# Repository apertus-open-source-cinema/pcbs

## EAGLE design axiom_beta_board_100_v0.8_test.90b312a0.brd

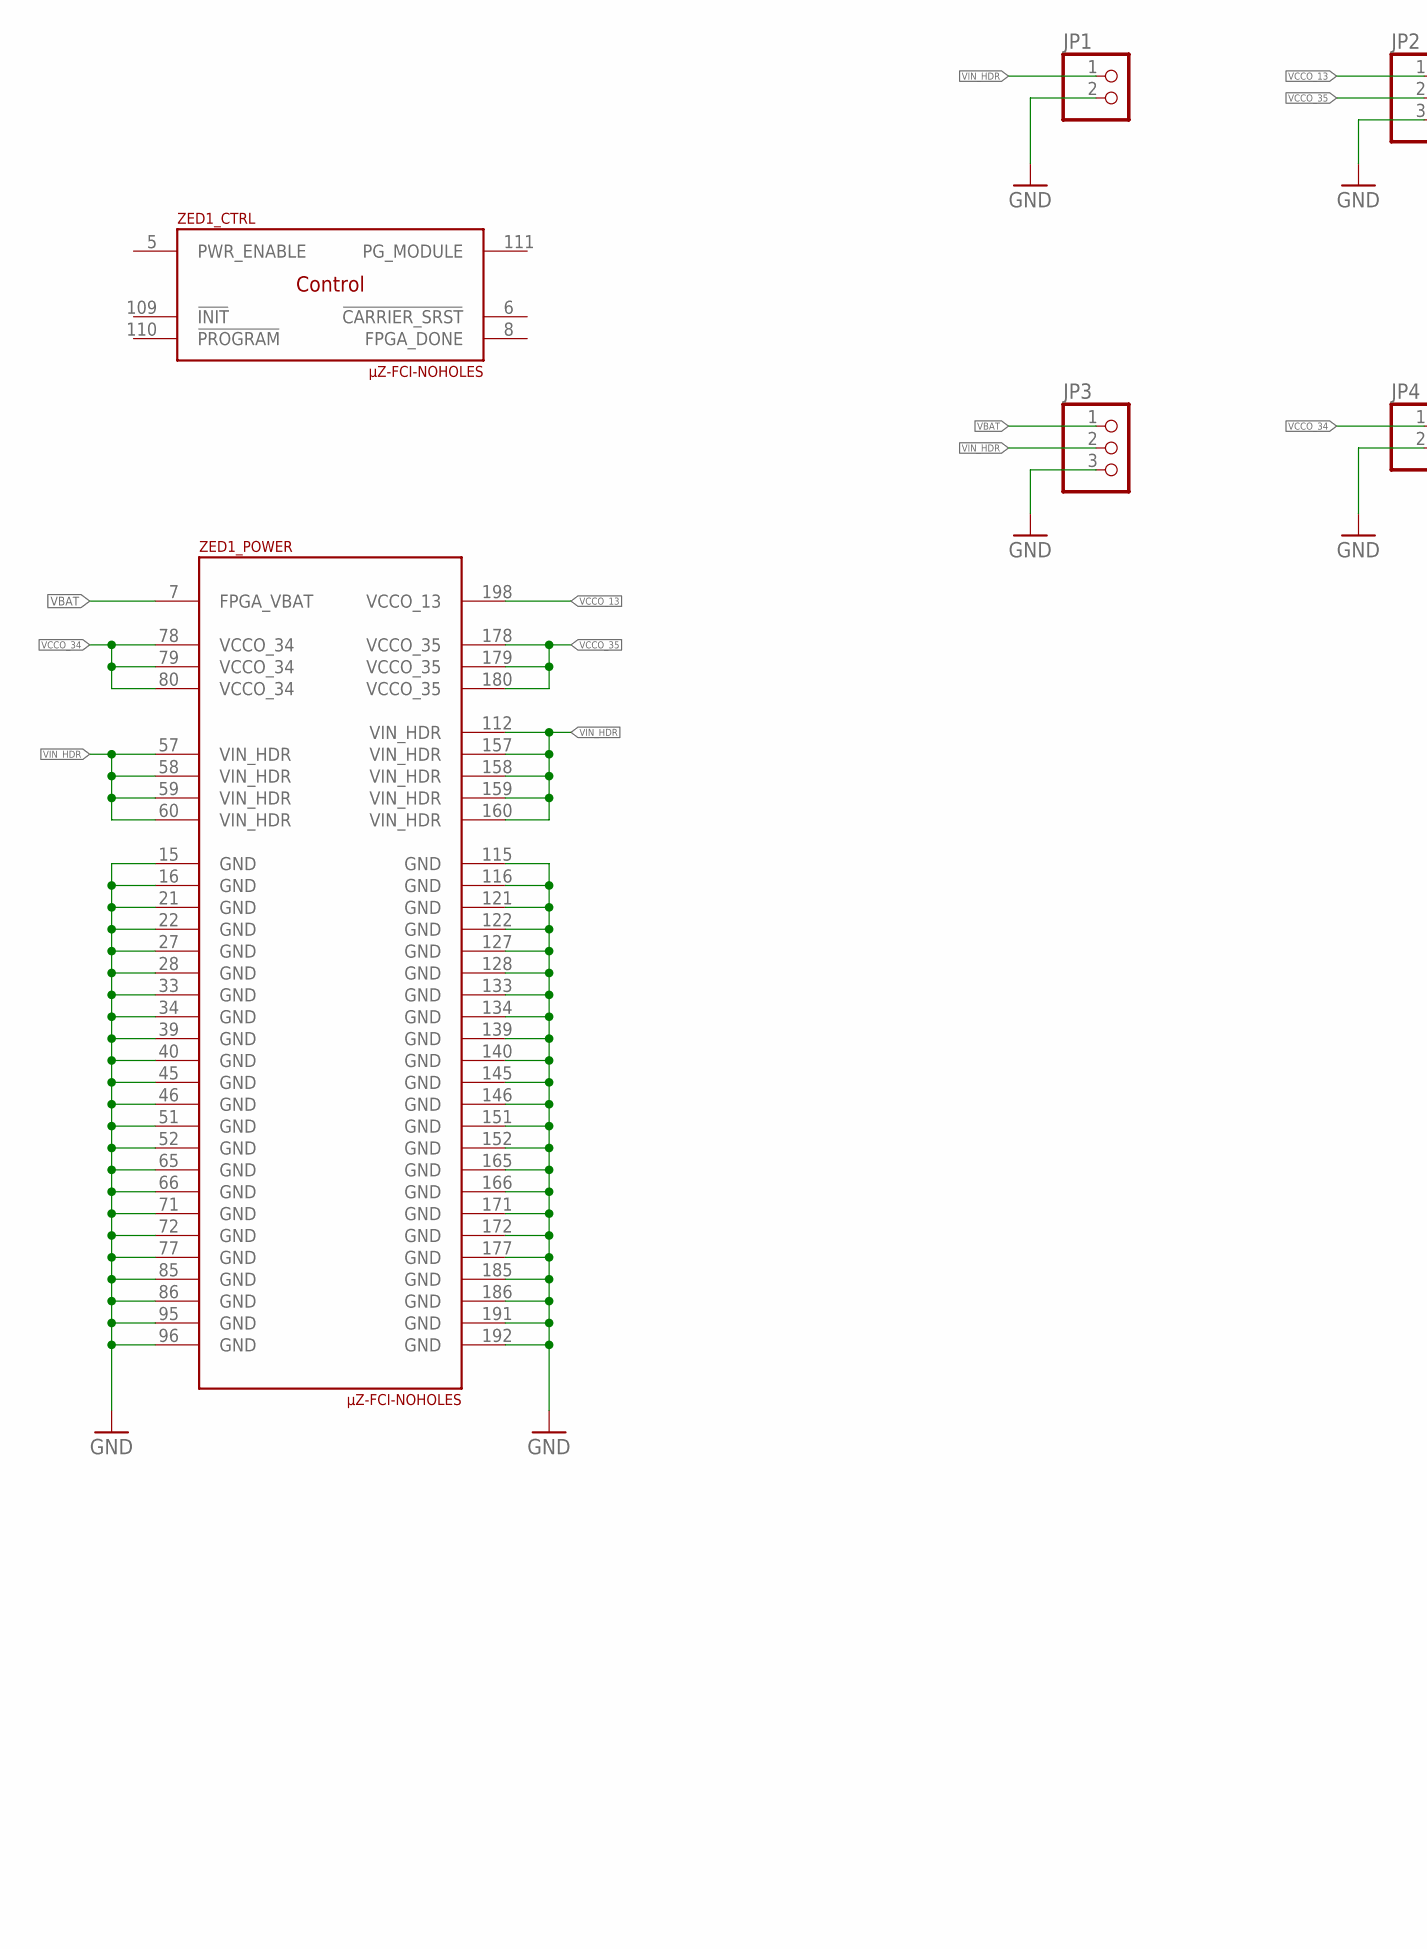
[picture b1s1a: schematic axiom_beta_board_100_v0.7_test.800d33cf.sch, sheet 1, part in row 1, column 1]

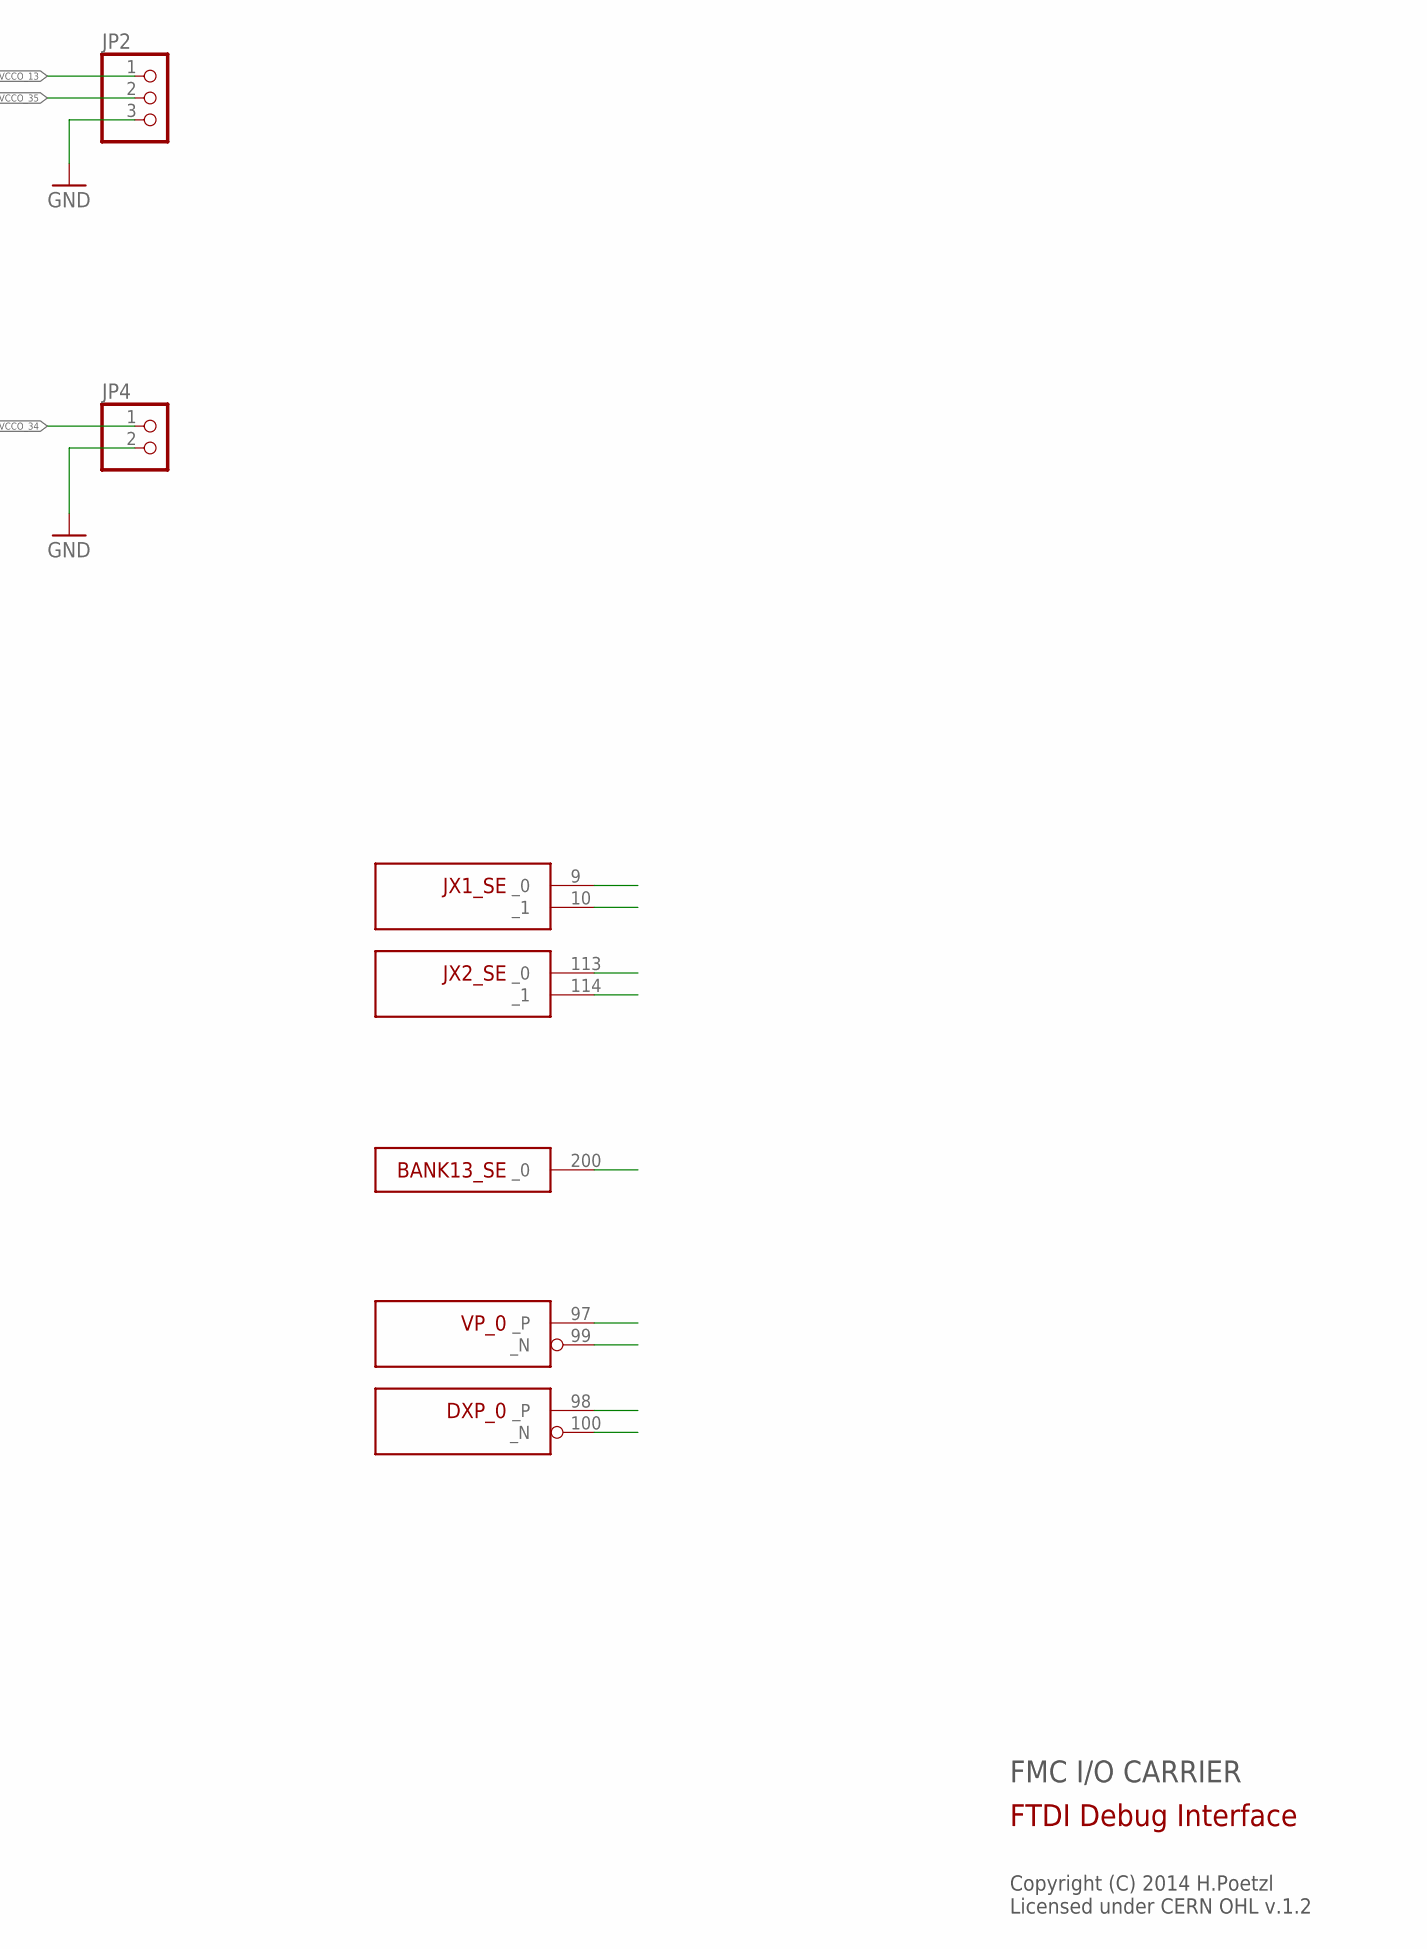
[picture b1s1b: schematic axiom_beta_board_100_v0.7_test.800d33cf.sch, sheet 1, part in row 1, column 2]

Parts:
JP1, JP4: PINHD-1X02_2.54; 1X02
JP2, JP3: PINHD-1X03_2.54; 1X03
ZED1: µZ-FCI-NOHOLES; µZ-NOHOLES

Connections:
VBAT: JP3.1, ZED1.7 (FPGA_VBAT)
VCCO_13: JP2.1, ZED1.198 (VCCO_13)
VCCO_34: JP4.1, ZED1.78 (VCCO_34), ZED1.79 (VCCO_34), ZED1.80 (VCCO_34)
VCCO_35: JP2.2, ZED1.178 (VCCO_35), ZED1.179 (VCCO_35), ZED1.180 (VCCO_35)
VIN_HDR: JP1.1, JP3.2, ZED1.57 (VIN_HDR), ZED1.58 (VIN_HDR), ZED1.59 (VIN_HDR), ZED1.60 (VIN_HDR), ZED1.112 (VIN_HDR), ZED1.157 (VIN_HDR), ZED1.158 (VIN_HDR), ZED1.159 (VIN_HDR), ZED1.160 (VIN_HDR)

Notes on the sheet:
FMC I/O CARRIER
Copyright (C) 2014 H.Poetzl Licensed under CERN OHL v.1.2
FTDI Debug Interface

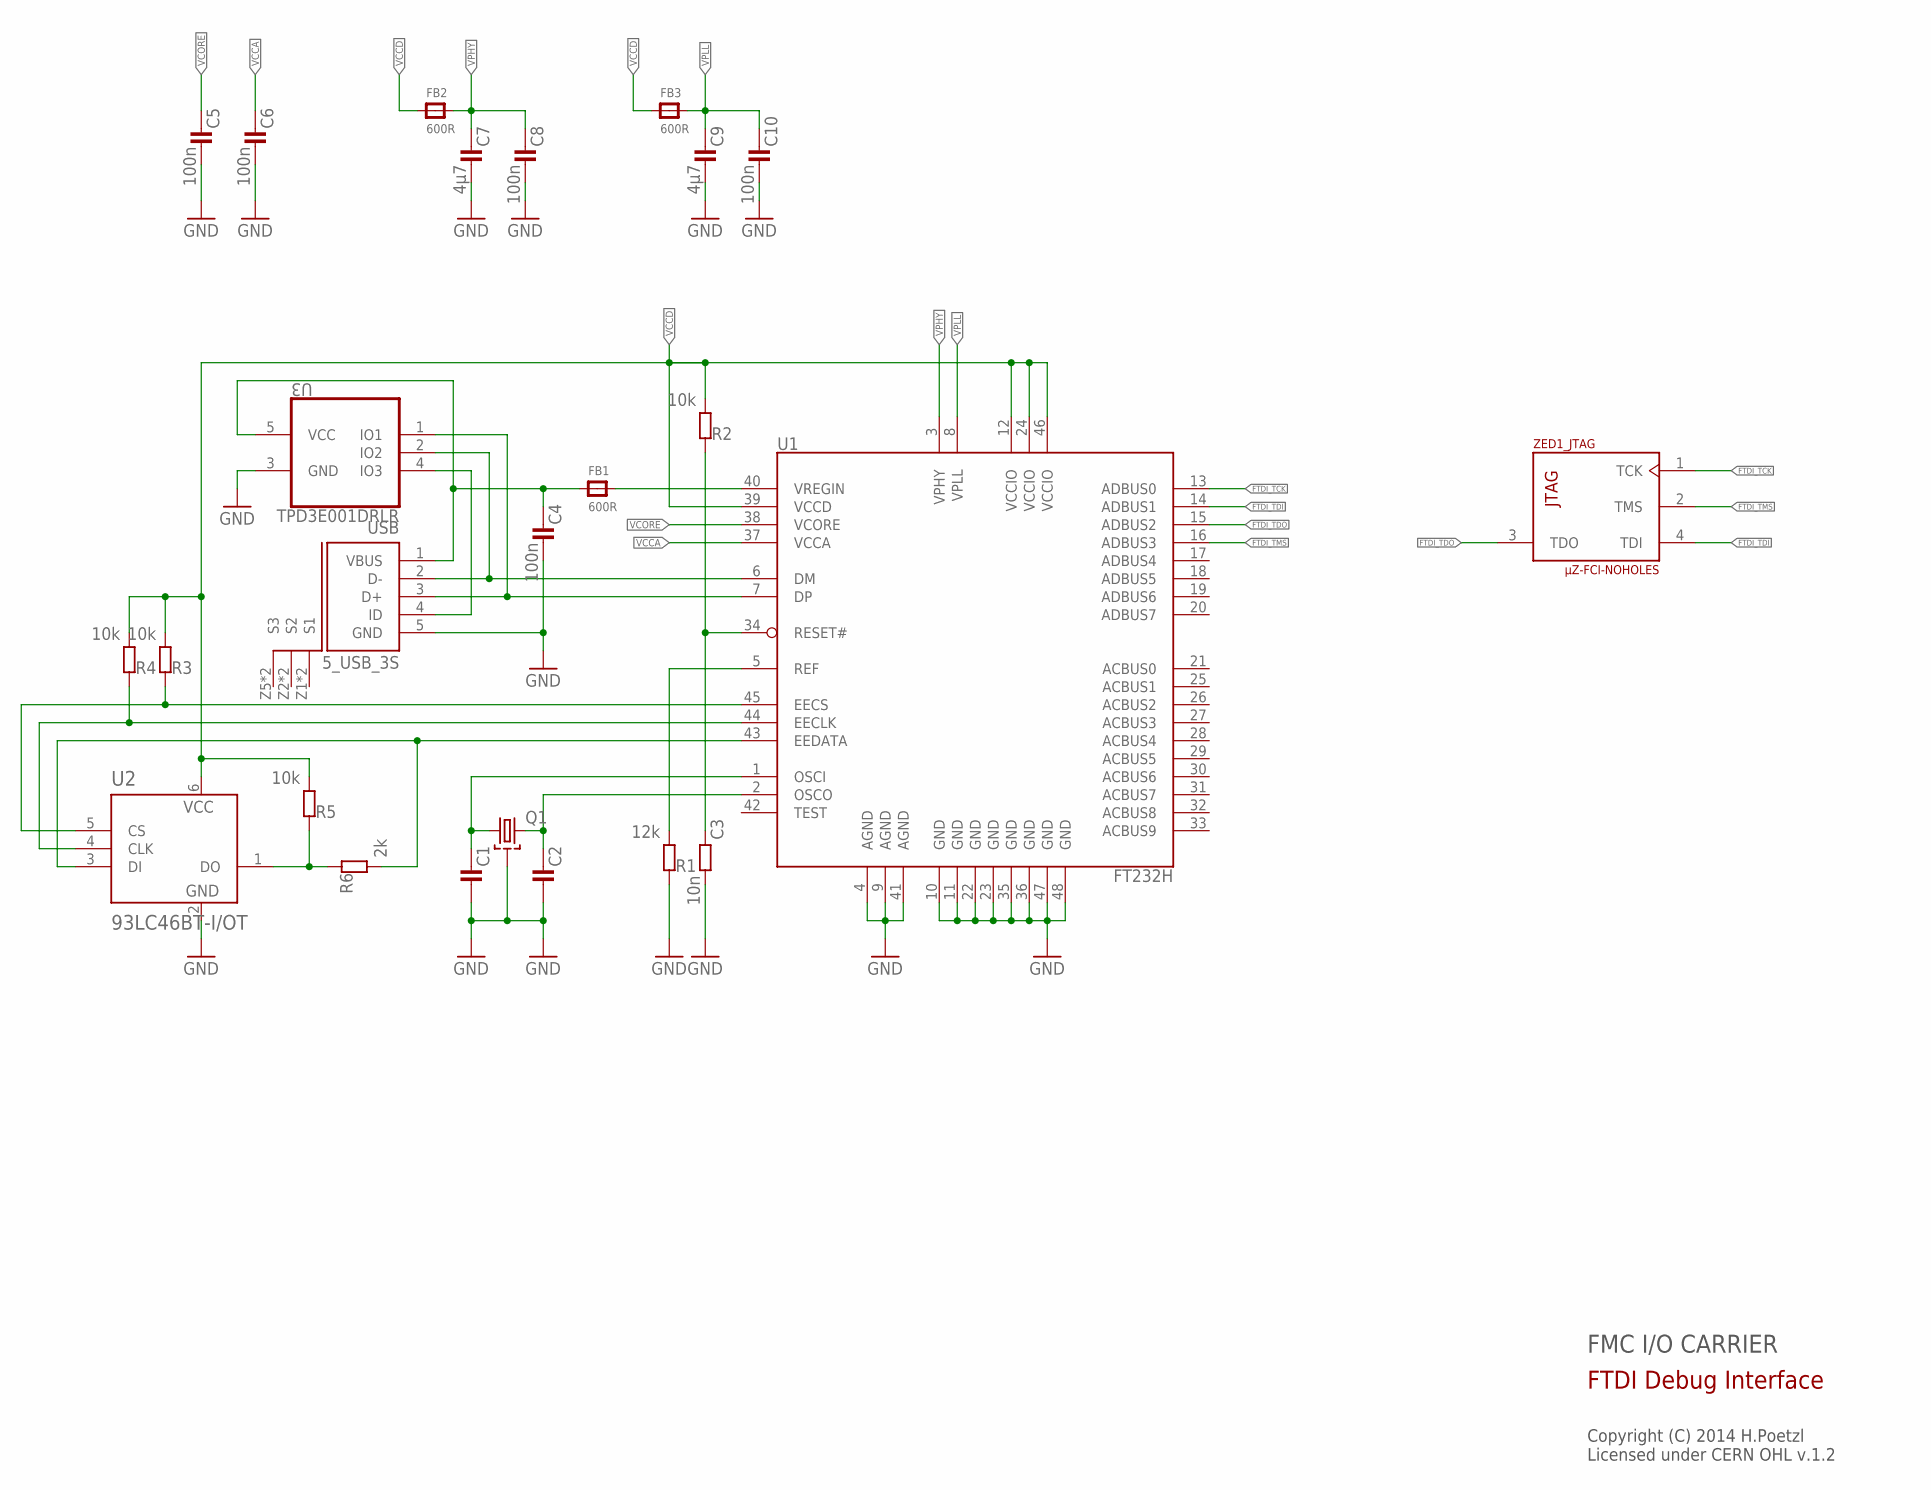
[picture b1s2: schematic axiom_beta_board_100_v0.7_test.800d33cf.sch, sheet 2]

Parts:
C1, C2: C0402-B; 0402-B
C3: 10n; 0402-B
C4: 100n; 0603-B
C5, C6, C8, C10: 100n; 0402-B
C7, C9: 4µ7; 0603-B
FB1, FB2, FB3: 600R; _0603MP
Q1: SMD-4P-2G-3.2X2.5; ABM8G
R1: 12k; 0402-B
R2, R3, R4, R5: 10k; 0402-B
R6: 2k; 0402-B
U1: FT232H; LQFP48
U2: 93LC46BT-I/OT; SOT95P280X145-6N
U3: TPD3E001DRLR; SOT50P160X60-5N
USB: 5_USB_3S; MICRO-AB-H-SMT
ZED1: µZ-FCI-NOHOLES; µZ-NOHOLES

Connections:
EE_CLK1: R4.1, U1.44 (EECLK), U2.4 (CLK)
EE_CS1: R3.1, U1.45 (EECS), U2.5 (CS)
EE_DATA1: R6.2, U1.43 (EEDATA), U2.3 (DI)
FTDI_D_N: U1.6 (DM), U3.2 (IO2), USB.2 (D-)
FTDI_D_P: U1.7 (DP), U3.1 (IO1), USB.3 (D+)
FTDI_TCK: U1.13 (ADBUS0), ZED1.1 (TCK)
FTDI_TDI: U1.14 (ADBUS1), ZED1.4 (TDI)
FTDI_TDO: U1.15 (ADBUS2), ZED1.3 (TDO)
FTDI_TMS: U1.16 (ADBUS3), ZED1.2 (TMS)
unnamed: R5.1, R6.1, U2.1 (DO)
unnamed: C1.1, Q1.1, U1.1 (OSCI)
unnamed: C2.1, Q1.3 (2), U1.2 (OSCO)
unnamed: C3.1, R2.1, U1.34 (RESET#)
unnamed: R1.2, U1.5 (REF)
unnamed: U3.4 (IO3), USB.4 (ID)
VBUS: C4.1, FB1.1, U3.5 (VCC), USB.1 (VBUS)
VCCA: C6.1, U1.37 (VCCA)
VCCD: FB2.1, FB3.1, R2.2, R3.2, R4.2, R5.2, U1.12 (VCCIO), U1.24 (VCCIO), U1.39 (VCCD), U1.46 (VCCIO), U2.6 (VCC)
VCORE: C5.1, U1.38 (VCORE)
VPHY: C7.1, C8.1, FB2.2, U1.3 (VPHY)
VPLL: C9.1, C10.1, FB3.2, U1.8 (VPLL)
VREGIN: FB1.2, U1.40 (VREGIN)

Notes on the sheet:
FMC I/O CARRIER
Copyright (C) 2014 H.Poetzl Licensed under CERN OHL v.1.2
FTDI Debug Interface

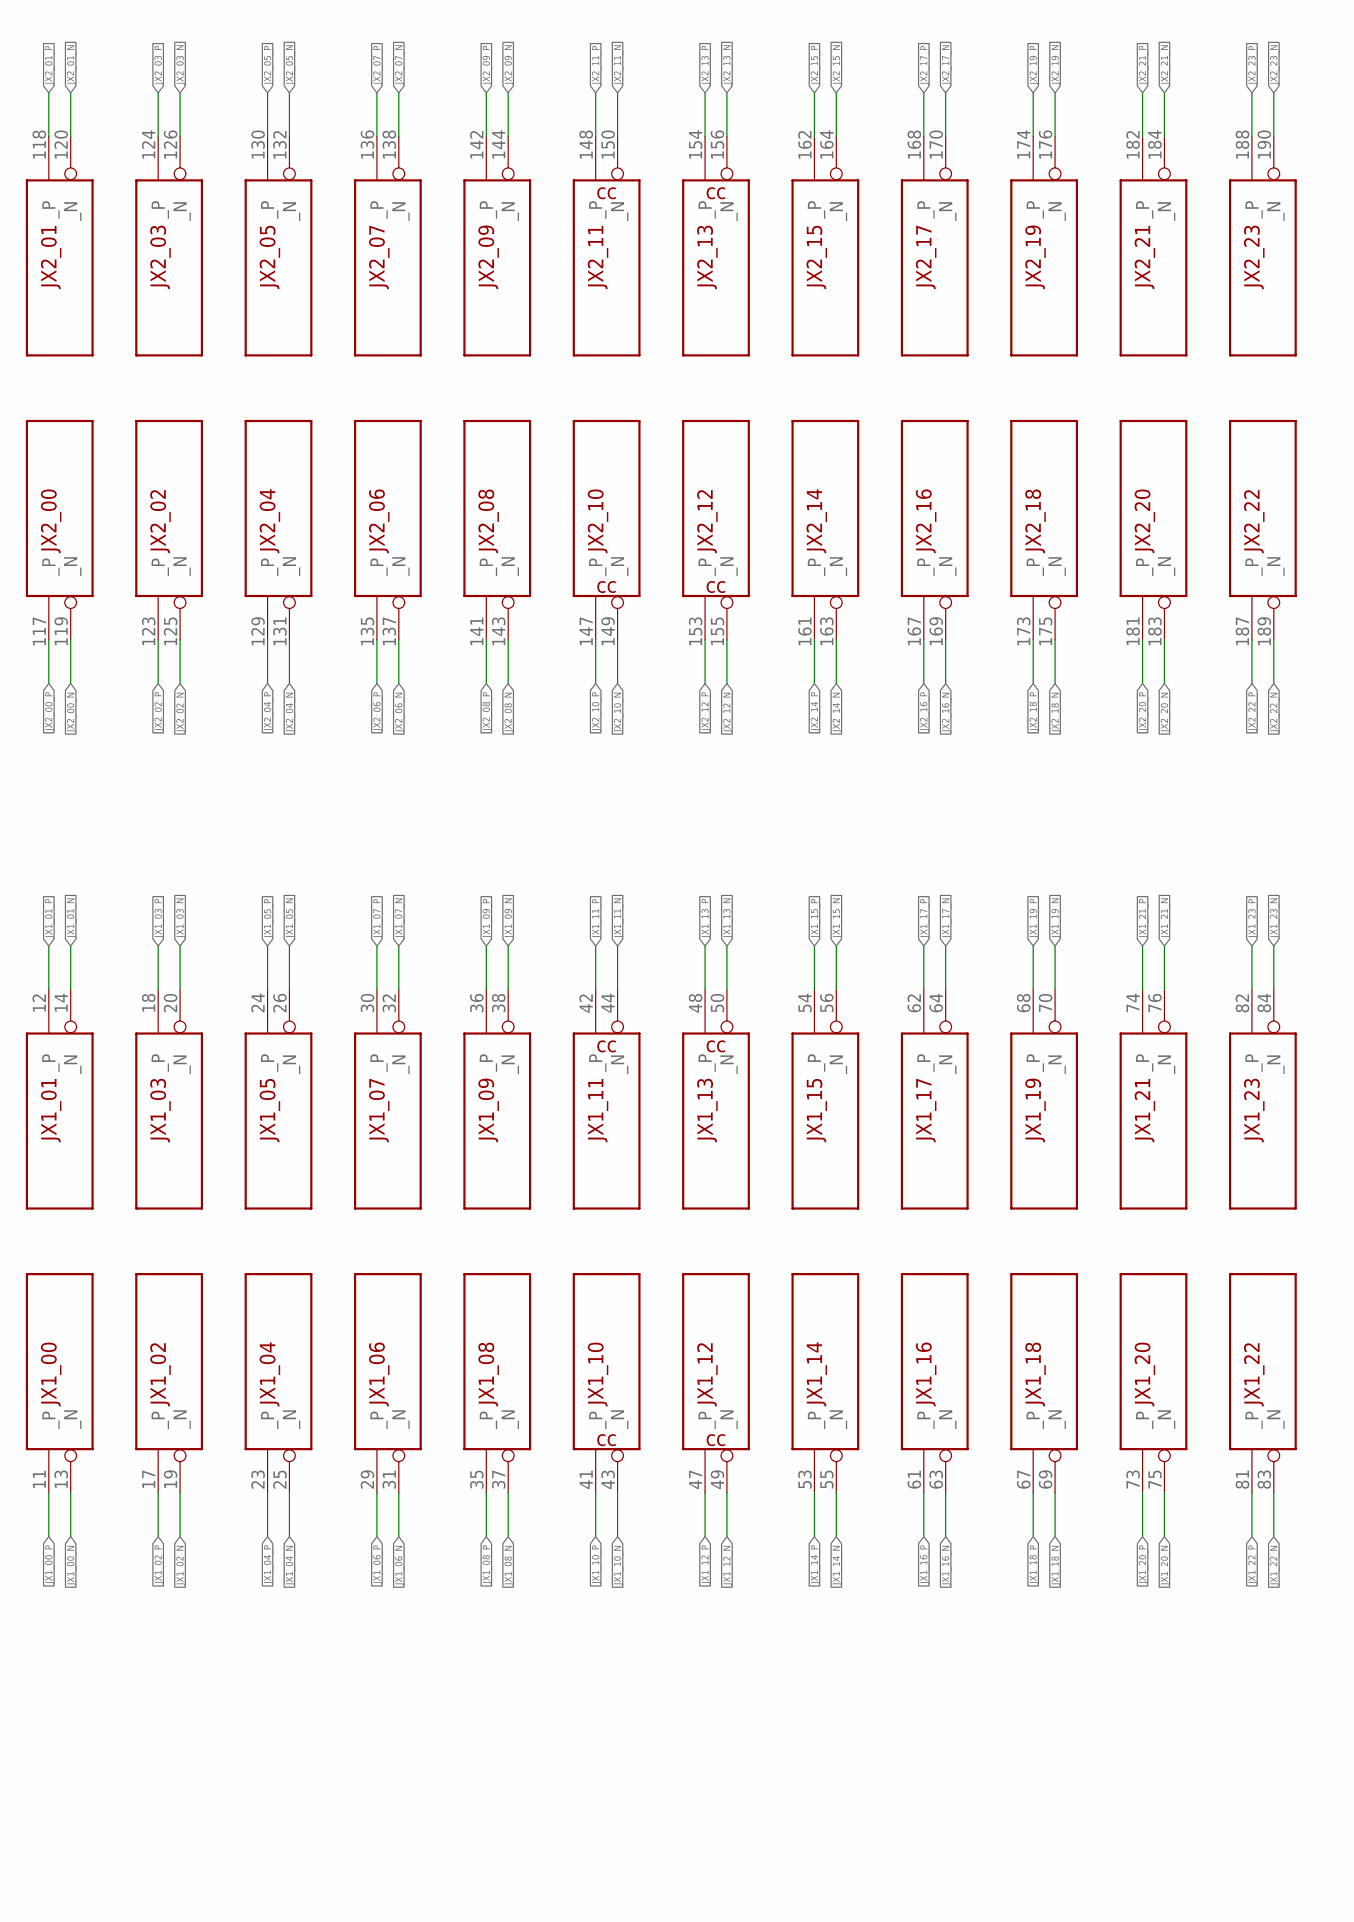
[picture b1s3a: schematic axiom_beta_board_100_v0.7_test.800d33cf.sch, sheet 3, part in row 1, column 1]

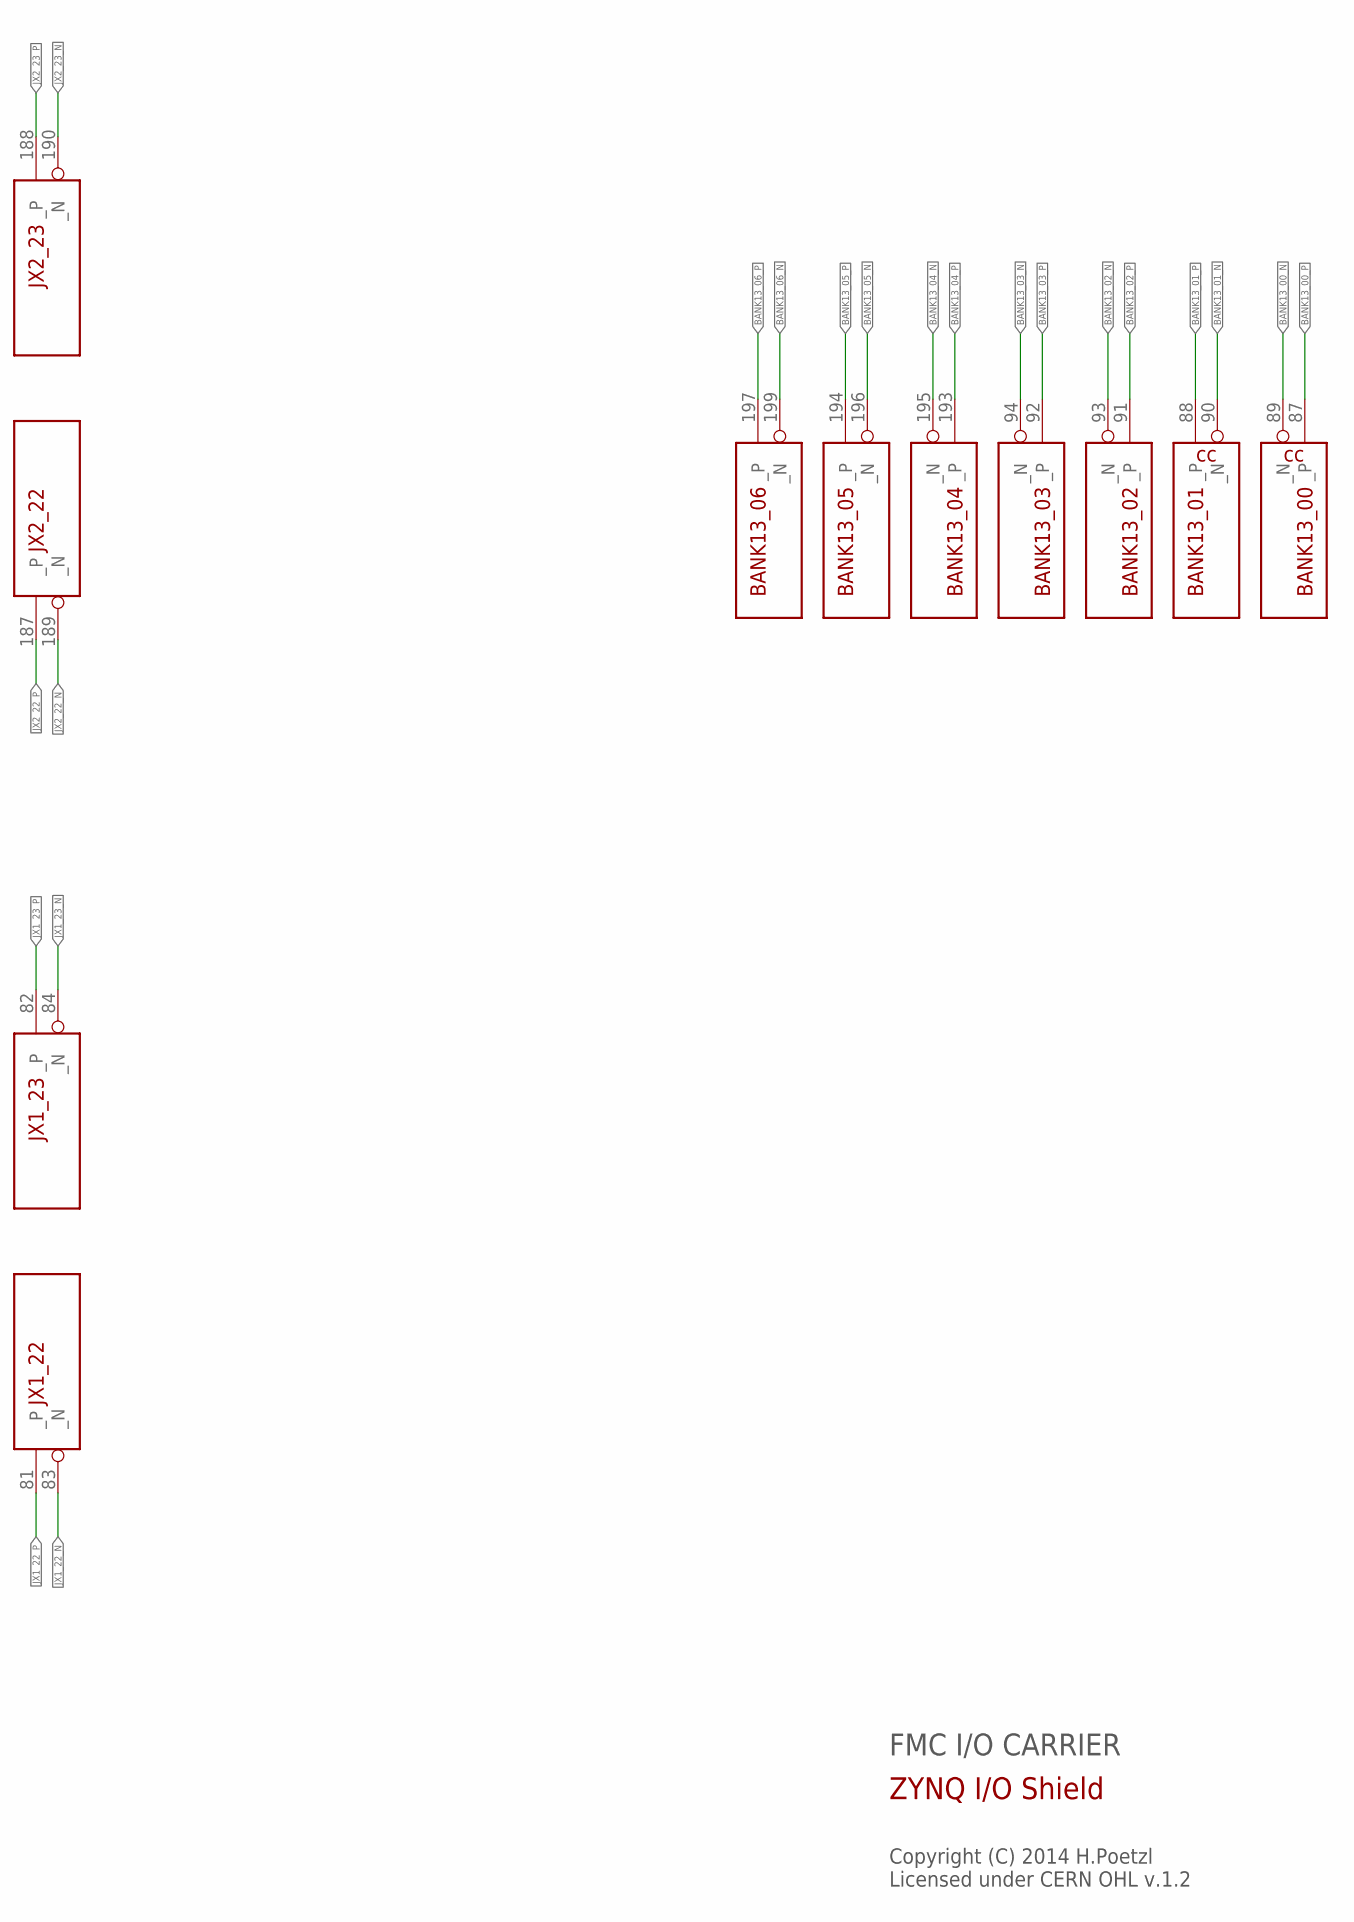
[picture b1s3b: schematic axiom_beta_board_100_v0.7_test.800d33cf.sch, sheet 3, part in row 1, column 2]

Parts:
ZED1: µZ-FCI-NOHOLES; µZ-NOHOLES

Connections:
BANK13_00_N: ZED1.89 (_N); also elsewhere on the board
BANK13_00_P: ZED1.87 (_P); also elsewhere on the board
BANK13_01_N: ZED1.90 (_N); also elsewhere on the board
BANK13_01_P: ZED1.88 (_P); also elsewhere on the board
BANK13_02_N: ZED1.93 (_N); also elsewhere on the board
BANK13_02_P: ZED1.91 (_P); also elsewhere on the board
BANK13_03_N: ZED1.94 (_N)
BANK13_03_P: ZED1.92 (_P)
BANK13_04_N: ZED1.195 (_N); also elsewhere on the board
BANK13_04_P: ZED1.193 (_P); also elsewhere on the board
BANK13_05_N: ZED1.196 (_N); also elsewhere on the board
BANK13_05_P: ZED1.194 (_P); also elsewhere on the board
BANK13_06_N: ZED1.199 (_N); also elsewhere on the board
BANK13_06_P: ZED1.197 (_P); also elsewhere on the board
JX1_00_N: ZED1.13 (_N); also elsewhere on the board
JX1_00_P: ZED1.11 (_P); also elsewhere on the board
JX1_01_N: ZED1.14 (_N); also elsewhere on the board
JX1_01_P: ZED1.12 (_P); also elsewhere on the board
JX1_02_N: ZED1.19 (_N); also elsewhere on the board
JX1_02_P: ZED1.17 (_P); also elsewhere on the board
JX1_03_N: ZED1.20 (_N); also elsewhere on the board
JX1_03_P: ZED1.18 (_P); also elsewhere on the board
JX1_04_N: ZED1.25 (_N); also elsewhere on the board
JX1_04_P: ZED1.23 (_P); also elsewhere on the board
JX1_05_N: ZED1.26 (_N); also elsewhere on the board
JX1_05_P: ZED1.24 (_P); also elsewhere on the board
JX1_06_N: ZED1.31 (_N); also elsewhere on the board
JX1_06_P: ZED1.29 (_P); also elsewhere on the board
JX1_07_N: ZED1.32 (_N); also elsewhere on the board
JX1_07_P: ZED1.30 (_P); also elsewhere on the board
JX1_08_N: ZED1.37 (_N); also elsewhere on the board
JX1_08_P: ZED1.35 (_P); also elsewhere on the board
JX1_09_N: ZED1.38 (_N); also elsewhere on the board
JX1_09_P: ZED1.36 (_P); also elsewhere on the board
JX1_10_N: ZED1.43 (_N); also elsewhere on the board
JX1_10_P: ZED1.41 (_P); also elsewhere on the board
JX1_11_N: ZED1.44 (_N); also elsewhere on the board
JX1_11_P: ZED1.42 (_P); also elsewhere on the board
JX1_12_N: ZED1.49 (_N); also elsewhere on the board
JX1_12_P: ZED1.47 (_P); also elsewhere on the board
JX1_13_N: ZED1.50 (_N); also elsewhere on the board
JX1_13_P: ZED1.48 (_P); also elsewhere on the board
JX1_14_N: ZED1.55 (_N); also elsewhere on the board
JX1_14_P: ZED1.53 (_P); also elsewhere on the board
JX1_15_N: ZED1.56 (_N); also elsewhere on the board
JX1_15_P: ZED1.54 (_P); also elsewhere on the board
JX1_16_N: ZED1.63 (_N); also elsewhere on the board
JX1_16_P: ZED1.61 (_P); also elsewhere on the board
JX1_17_N: ZED1.64 (_N); also elsewhere on the board
JX1_17_P: ZED1.62 (_P); also elsewhere on the board
JX1_18_N: ZED1.69 (_N); also elsewhere on the board
JX1_18_P: ZED1.67 (_P); also elsewhere on the board
JX1_19_N: ZED1.70 (_N); also elsewhere on the board
JX1_19_P: ZED1.68 (_P); also elsewhere on the board
JX1_20_N: ZED1.75 (_N); also elsewhere on the board
JX1_20_P: ZED1.73 (_P); also elsewhere on the board
JX1_21_N: ZED1.76 (_N); also elsewhere on the board
JX1_21_P: ZED1.74 (_P); also elsewhere on the board
JX1_22_N: ZED1.83 (_N); also elsewhere on the board
JX1_22_P: ZED1.81 (_P); also elsewhere on the board
JX1_23_N: ZED1.84 (_N); also elsewhere on the board
JX1_23_P: ZED1.82 (_P); also elsewhere on the board
JX2_00_N: ZED1.119 (_N); also elsewhere on the board
JX2_00_P: ZED1.117 (_P); also elsewhere on the board
JX2_01_N: ZED1.120 (_N); also elsewhere on the board
JX2_01_P: ZED1.118 (_P); also elsewhere on the board
JX2_02_N: ZED1.125 (_N); also elsewhere on the board
JX2_02_P: ZED1.123 (_P); also elsewhere on the board
JX2_03_N: ZED1.126 (_N); also elsewhere on the board
JX2_03_P: ZED1.124 (_P); also elsewhere on the board
JX2_04_N: ZED1.131 (_N); also elsewhere on the board
JX2_04_P: ZED1.129 (_P); also elsewhere on the board
JX2_05_N: ZED1.132 (_N); also elsewhere on the board
JX2_05_P: ZED1.130 (_P); also elsewhere on the board
JX2_06_N: ZED1.137 (_N); also elsewhere on the board
JX2_06_P: ZED1.135 (_P); also elsewhere on the board
JX2_07_N: ZED1.138 (_N); also elsewhere on the board
JX2_07_P: ZED1.136 (_P); also elsewhere on the board
JX2_08_N: ZED1.143 (_N); also elsewhere on the board
JX2_08_P: ZED1.141 (_P); also elsewhere on the board
JX2_09_N: ZED1.144 (_N); also elsewhere on the board
JX2_09_P: ZED1.142 (_P); also elsewhere on the board
JX2_10_N: ZED1.149 (_N); also elsewhere on the board
JX2_10_P: ZED1.147 (_P); also elsewhere on the board
JX2_11_N: ZED1.150 (_N); also elsewhere on the board
JX2_11_P: ZED1.148 (_P); also elsewhere on the board
JX2_12_N: ZED1.155 (_N); also elsewhere on the board
JX2_12_P: ZED1.153 (_P); also elsewhere on the board
JX2_13_N: ZED1.156 (_N); also elsewhere on the board
JX2_13_P: ZED1.154 (_P); also elsewhere on the board
JX2_14_N: ZED1.163 (_N); also elsewhere on the board
JX2_14_P: ZED1.161 (_P); also elsewhere on the board
JX2_15_N: ZED1.164 (_N); also elsewhere on the board
JX2_15_P: ZED1.162 (_P); also elsewhere on the board
JX2_16_N: ZED1.169 (_N); also elsewhere on the board
JX2_16_P: ZED1.167 (_P); also elsewhere on the board
JX2_17_N: ZED1.170 (_N); also elsewhere on the board
JX2_17_P: ZED1.168 (_P); also elsewhere on the board
JX2_18_N: ZED1.175 (_N); also elsewhere on the board
JX2_18_P: ZED1.173 (_P); also elsewhere on the board
JX2_19_N: ZED1.176 (_N); also elsewhere on the board
JX2_19_P: ZED1.174 (_P); also elsewhere on the board
JX2_20_N: ZED1.183 (_N); also elsewhere on the board
JX2_20_P: ZED1.181 (_P); also elsewhere on the board
JX2_21_N: ZED1.184 (_N); also elsewhere on the board
JX2_21_P: ZED1.182 (_P); also elsewhere on the board
JX2_22_N: ZED1.189 (_N); also elsewhere on the board
JX2_22_P: ZED1.187 (_P); also elsewhere on the board
JX2_23_N: ZED1.190 (_N); also elsewhere on the board
JX2_23_P: ZED1.188 (_P); also elsewhere on the board

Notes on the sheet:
FMC I/O CARRIER
Copyright (C) 2014 H.Poetzl Licensed under CERN OHL v.1.2
ZYNQ I/O Shield

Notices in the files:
axiom_beta_board_100_v0.8_test.90b312a0.brd:
Copyright (C) 2014 Herbert Pötzl
axiom_beta_center_solder_on_v0.1-default.32b33ea7.brd:
Copyright (C) 2016 Herbert Pötzl
axiom_beta_imu_cso_v0.1_r1.1-default.265cd33e.brd:
Copyright (C) 2017 Herbert Pötzl
axiom_beta_interface_cmv12000_v0.3-default.d94e37f1.brd:
Copyright (C) 2014 Herbert Poetzl
axiom_beta_interface_dummy_v0.11-default.33cbe5a0.brd:
Copyright (C) 2015 Herbert Pötzl
